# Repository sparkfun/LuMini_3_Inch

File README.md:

SparkFun LuMini 3 Inch Ring
========================================

[*LuMini LED Ring - 3 Inch (COM-14965)*](https://www.sparkfun.com/products/14965)

The LuMini rings are a great way to add high density light rings to your project. They use APA102 LEDs to provide bright colors and fast data rates.

Repository Contents
-------------------

* **/Firmware** - Example code 
* **/Hardware** - Eagle design files (.brd, .sch)

Documentation
--------------
* **[Installing an Arduino Library Guide](https://learn.sparkfun.com/tutorials/installing-an-arduino-library)** - Basic information on how to install an Arduino library.
* **[Library Repository](https://github.com/FastLED/FastLED)** - Arduino library for the APA102.
* **[Hookup Guide](https://learn.sparkfun.com/tutorials/lumini-ring-hookup-guide)** - Basic hookup guide for the LuMini Rings.

Product Versions
----------------
* [COM-14965](https://www.sparkfun.com/products/14965)- 3 Inch LED Ring

License Information
-------------------

This product is _**open source**_! 

Please review the LICENSE.md file for license information. 

If you have any questions or concerns on licensing, please contact techsupport@sparkfun.com.

Distributed as-is; no warranty is given.

- Your friends at SparkFun.

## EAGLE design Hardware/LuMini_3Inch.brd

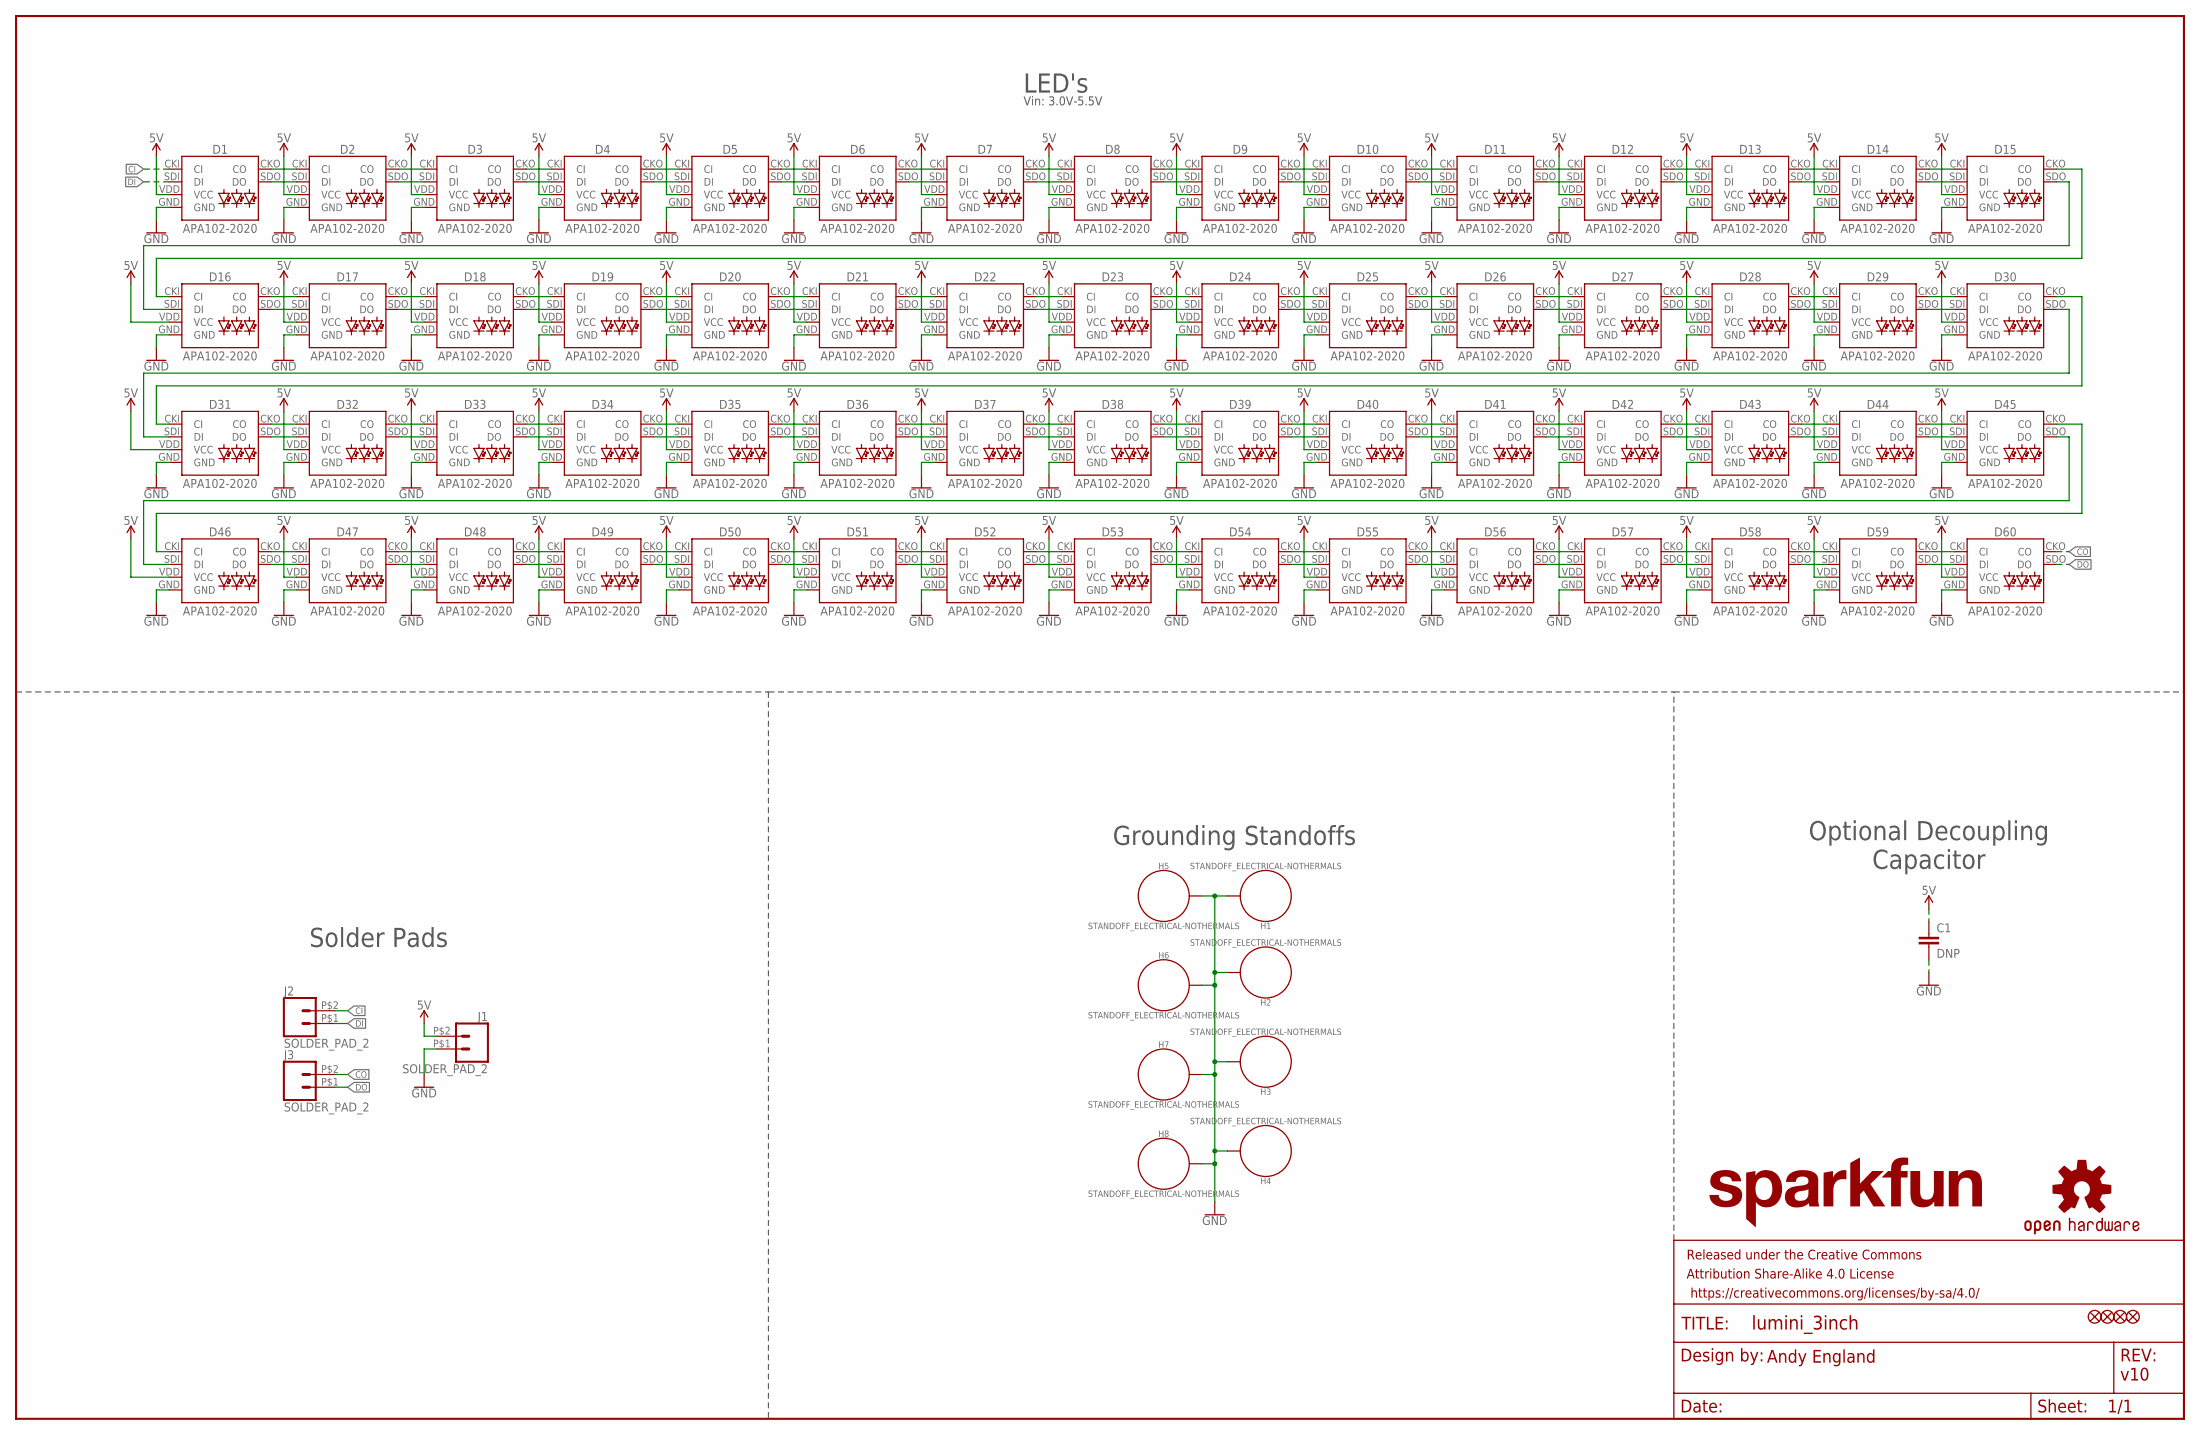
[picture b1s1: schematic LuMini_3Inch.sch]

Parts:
C1: DNP; 1206
D1, D2, D3, D4, D5, D6, D7, D8, D9, D10, D11, D12, D13, D14, D15, D16, D17, D18, D19, D20, D21, D22, D23, D24, D25, D26, D27, D28, D29, D30, D31, D32, D33, D34, D35, D36, D37, D38, D39, D40, D41, D42, D43, D44, D45, D46, D47, D48, D49, D50, D51, D52, D53, D54, D55, D56, D57, D58, D59, D60: APA102-2020
FD1, FD2, FD3, FD4: FIDUCIALUFIDUCIAL; FIDUCIAL-MICRO
FRAME1: FRAME-LEDGER; CREATIVE_COMMONS
H1, H2, H3, H4, H5, H6, H7, H8: STANDOFF_ELECTRICAL-NOTHERMALS; STANDOFF-ELECTRICAL-NOTHERMALS
J1, J2, J3: SOLDER_PAD_2
LOGO1: OSHW-LOGOS; OSHW-LOGO-S
LOGO2: SFE_LOGO_NAME.1_INCH; SFE_LOGO_NAME_.1

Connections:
5V: C1.1, D1.VDD (VCC), D2.VDD (VCC), D3.VDD (VCC), D4.VDD (VCC), D5.VDD (VCC), D6.VDD (VCC), D7.VDD (VCC), D8.VDD (VCC), D9.VDD (VCC), D10.VDD (VCC), D11.VDD (VCC), D12.VDD (VCC), D13.VDD (VCC), D14.VDD (VCC), D15.VDD (VCC), D16.VDD (VCC), D17.VDD (VCC), D18.VDD (VCC), D19.VDD (VCC), D20.VDD (VCC), D21.VDD (VCC), D22.VDD (VCC), D23.VDD (VCC), D24.VDD (VCC), D25.VDD (VCC), D26.VDD (VCC), D27.VDD (VCC), D28.VDD (VCC), D29.VDD (VCC), D30.VDD (VCC), D31.VDD (VCC), D32.VDD (VCC), D33.VDD (VCC), D34.VDD (VCC), D35.VDD (VCC), D36.VDD (VCC), D37.VDD (VCC), D38.VDD (VCC), D39.VDD (VCC), D40.VDD (VCC), D41.VDD (VCC), D42.VDD (VCC), D43.VDD (VCC), D44.VDD (VCC), D45.VDD (VCC), D46.VDD (VCC), D47.VDD (VCC), D48.VDD (VCC), D49.VDD (VCC), D50.VDD (VCC), D51.VDD (VCC), D52.VDD (VCC), D53.VDD (VCC), D54.VDD (VCC), D55.VDD (VCC), D56.VDD (VCC), D57.VDD (VCC), D58.VDD (VCC), D59.VDD (VCC), D60.VDD (VCC), J1.P$2 (2)
CI: D1.CKI (CI), J2.P$2 (2)
CO: D60.CKO (CO), J3.P$2 (2)
DI: D1.SDI (DI), J2.P$1 (1)
DO: D60.SDO (DO), J3.P$1 (1)
GND: C1.2, D1.GND, D2.GND, D3.GND, D4.GND, D5.GND, D6.GND, D7.GND, D8.GND, D9.GND, D10.GND, D11.GND, D12.GND, D13.GND, D14.GND, D15.GND, D16.GND, D17.GND, D18.GND, D19.GND, D20.GND, D21.GND, D22.GND, D23.GND, D24.GND, D25.GND, D26.GND, D27.GND, D28.GND, D29.GND, D30.GND, D31.GND, D32.GND, D33.GND, D34.GND, D35.GND, D36.GND, D37.GND, D38.GND, D39.GND, D40.GND, D41.GND, D42.GND, D43.GND, D44.GND, D45.GND, D46.GND, D47.GND, D48.GND, D49.GND, D50.GND, D51.GND, D52.GND, D53.GND, D54.GND, D55.GND, D56.GND, D57.GND, D58.GND, D59.GND, D60.GND, H1.P1, H2.P1, H3.P1, H4.P1, H5.P1, H6.P1, H7.P1, H8.P1, J1.P$1 (1)
unnamed: D4.CKO (CO), D5.CKI (CI)
unnamed: D1.CKO (CO), D2.CKI (CI)
unnamed: D1.SDO (DO), D2.SDI (DI)
unnamed: D2.CKO (CO), D3.CKI (CI)
unnamed: D2.SDO (DO), D3.SDI (DI)
unnamed: D3.CKO (CO), D4.CKI (CI)
unnamed: D3.SDO (DO), D4.SDI (DI)
unnamed: D4.SDO (DO), D5.SDI (DI)
unnamed: D5.CKO (CO), D6.CKI (CI)
unnamed: D5.SDO (DO), D6.SDI (DI)
unnamed: D6.CKO (CO), D7.CKI (CI)
unnamed: D6.SDO (DO), D7.SDI (DI)
unnamed: D7.CKO (CO), D8.CKI (CI)
unnamed: D7.SDO (DO), D8.SDI (DI)
unnamed: D16.SDO (DO), D17.SDI (DI)
unnamed: D20.SDO (DO), D21.SDI (DI)
unnamed: D9.CKO (CO), D10.CKI (CI)
unnamed: D9.SDO (DO), D10.SDI (DI)
unnamed: D10.CKO (CO), D11.CKI (CI)
unnamed: D10.SDO (DO), D11.SDI (DI)
unnamed: D11.CKO (CO), D12.CKI (CI)
unnamed: D11.SDO (DO), D12.SDI (DI)
unnamed: D12.CKO (CO), D13.CKI (CI)
unnamed: D12.SDO (DO), D13.SDI (DI)
unnamed: D13.CKO (CO), D14.CKI (CI)
unnamed: D13.SDO (DO), D14.SDI (DI)
unnamed: D14.CKO (CO), D15.CKI (CI)
unnamed: D14.SDO (DO), D15.SDI (DI)
unnamed: D45.CKO (CO), D46.CKI (CI)
unnamed: D30.CKO (CO), D31.CKI (CI)
unnamed: D8.CKO (CO), D9.CKI (CI)
unnamed: D8.SDO (DO), D9.SDI (DI)
unnamed: D17.CKO (CO), D18.CKI (CI)
unnamed: D17.SDO (DO), D18.SDI (DI)
unnamed: D18.CKO (CO), D19.CKI (CI)
unnamed: D18.SDO (DO), D19.SDI (DI)
unnamed: D19.CKO (CO), D20.CKI (CI)
unnamed: D19.SDO (DO), D20.SDI (DI)
unnamed: D30.SDO (DO), D31.SDI (DI)
unnamed: D15.CKO (CO), D16.CKI (CI)
unnamed: D16.CKO (CO), D17.CKI (CI)
unnamed: D21.CKO (CO), D22.CKI (CI)
unnamed: D21.SDO (DO), D22.SDI (DI)
unnamed: D22.CKO (CO), D23.CKI (CI)
unnamed: D22.SDO (DO), D23.SDI (DI)
unnamed: D23.CKO (CO), D24.CKI (CI)
unnamed: D23.SDO (DO), D24.SDI (DI)
unnamed: D24.CKO (CO), D25.CKI (CI)
unnamed: D24.SDO (DO), D25.SDI (DI)
unnamed: D25.CKO (CO), D26.CKI (CI)
unnamed: D25.SDO (DO), D26.SDI (DI)
unnamed: D26.CKO (CO), D27.CKI (CI)
unnamed: D26.SDO (DO), D27.SDI (DI)
unnamed: D27.CKO (CO), D28.CKI (CI)
unnamed: D27.SDO (DO), D28.SDI (DI)
unnamed: D29.CKO (CO), D30.CKI (CI)
unnamed: D29.SDO (DO), D30.SDI (DI)
unnamed: D15.SDO (DO), D16.SDI (DI)
unnamed: D45.SDO (DO), D46.SDI (DI)
unnamed: D31.CKO (CO), D32.CKI (CI)
unnamed: D31.SDO (DO), D32.SDI (DI)
unnamed: D32.CKO (CO), D33.CKI (CI)
unnamed: D32.SDO (DO), D33.SDI (DI)
unnamed: D33.CKO (CO), D34.CKI (CI)
unnamed: D33.SDO (DO), D34.SDI (DI)
unnamed: D34.CKO (CO), D35.CKI (CI)
unnamed: D34.SDO (DO), D35.SDI (DI)
unnamed: D35.CKO (CO), D36.CKI (CI)
unnamed: D35.SDO (DO), D36.SDI (DI)
unnamed: D37.CKO (CO), D38.CKI (CI)
unnamed: D37.SDO (DO), D38.SDI (DI)
unnamed: D38.SDO (DO), D39.SDI (DI)
unnamed: D39.CKO (CO), D40.CKI (CI)
unnamed: D39.SDO (DO), D40.SDI (DI)
unnamed: D38.CKO (CO), D39.CKI (CI)
unnamed: D28.CKO (CO), D29.CKI (CI)
unnamed: D28.SDO (DO), D29.SDI (DI)
unnamed: D36.SDO (DO), D37.SDI (DI)
unnamed: D36.CKO (CO), D37.CKI (CI)
unnamed: D40.CKO (CO), D41.CKI (CI)
unnamed: D40.SDO (DO), D41.SDI (DI)
unnamed: D41.CKO (CO), D42.CKI (CI)
unnamed: D41.SDO (DO), D42.SDI (DI)
unnamed: D42.CKO (CO), D43.CKI (CI)
unnamed: D42.SDO (DO), D43.SDI (DI)
unnamed: D43.CKO (CO), D44.CKI (CI)
unnamed: D43.SDO (DO), D44.SDI (DI)
unnamed: D44.CKO (CO), D45.CKI (CI)
unnamed: D44.SDO (DO), D45.SDI (DI)
unnamed: D46.CKO (CO), D47.CKI (CI)
unnamed: D46.SDO (DO), D47.SDI (DI)
unnamed: D47.CKO (CO), D48.CKI (CI)
unnamed: D47.SDO (DO), D48.SDI (DI)
unnamed: D49.CKO (CO), D50.CKI (CI)
unnamed: D49.SDO (DO), D50.SDI (DI)
unnamed: D50.CKO (CO), D51.CKI (CI)
unnamed: D50.SDO (DO), D51.SDI (DI)
unnamed: D51.CKO (CO), D52.CKI (CI)
unnamed: D51.SDO (DO), D52.SDI (DI)
unnamed: D52.CKO (CO), D53.CKI (CI)
unnamed: D52.SDO (DO), D53.SDI (DI)
unnamed: D53.CKO (CO), D54.CKI (CI)
unnamed: D53.SDO (DO), D54.SDI (DI)
unnamed: D54.CKO (CO), D55.CKI (CI)
unnamed: D54.SDO (DO), D55.SDI (DI)
unnamed: D55.CKO (CO), D56.CKI (CI)
unnamed: D55.SDO (DO), D56.SDI (DI)
unnamed: D57.CKO (CO), D58.CKI (CI)
unnamed: D57.SDO (DO), D58.SDI (DI)
unnamed: D58.SDO (DO), D59.SDI (DI)
unnamed: D59.CKO (CO), D60.CKI (CI)
unnamed: D59.SDO (DO), D60.SDI (DI)
unnamed: D58.CKO (CO), D59.CKI (CI)
unnamed: D48.CKO (CO), D49.CKI (CI)
unnamed: D48.SDO (DO), D49.SDI (DI)
unnamed: D56.SDO (DO), D57.SDI (DI)
unnamed: D56.CKO (CO), D57.CKI (CI)
unnamed: D20.CKO (CO), D21.CKI (CI)

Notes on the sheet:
LED's
Grounding Standoffs
Andy England
v10
Vin: 3.0V-5.5V
Optional Decoupling Capacitor
Solder Pads

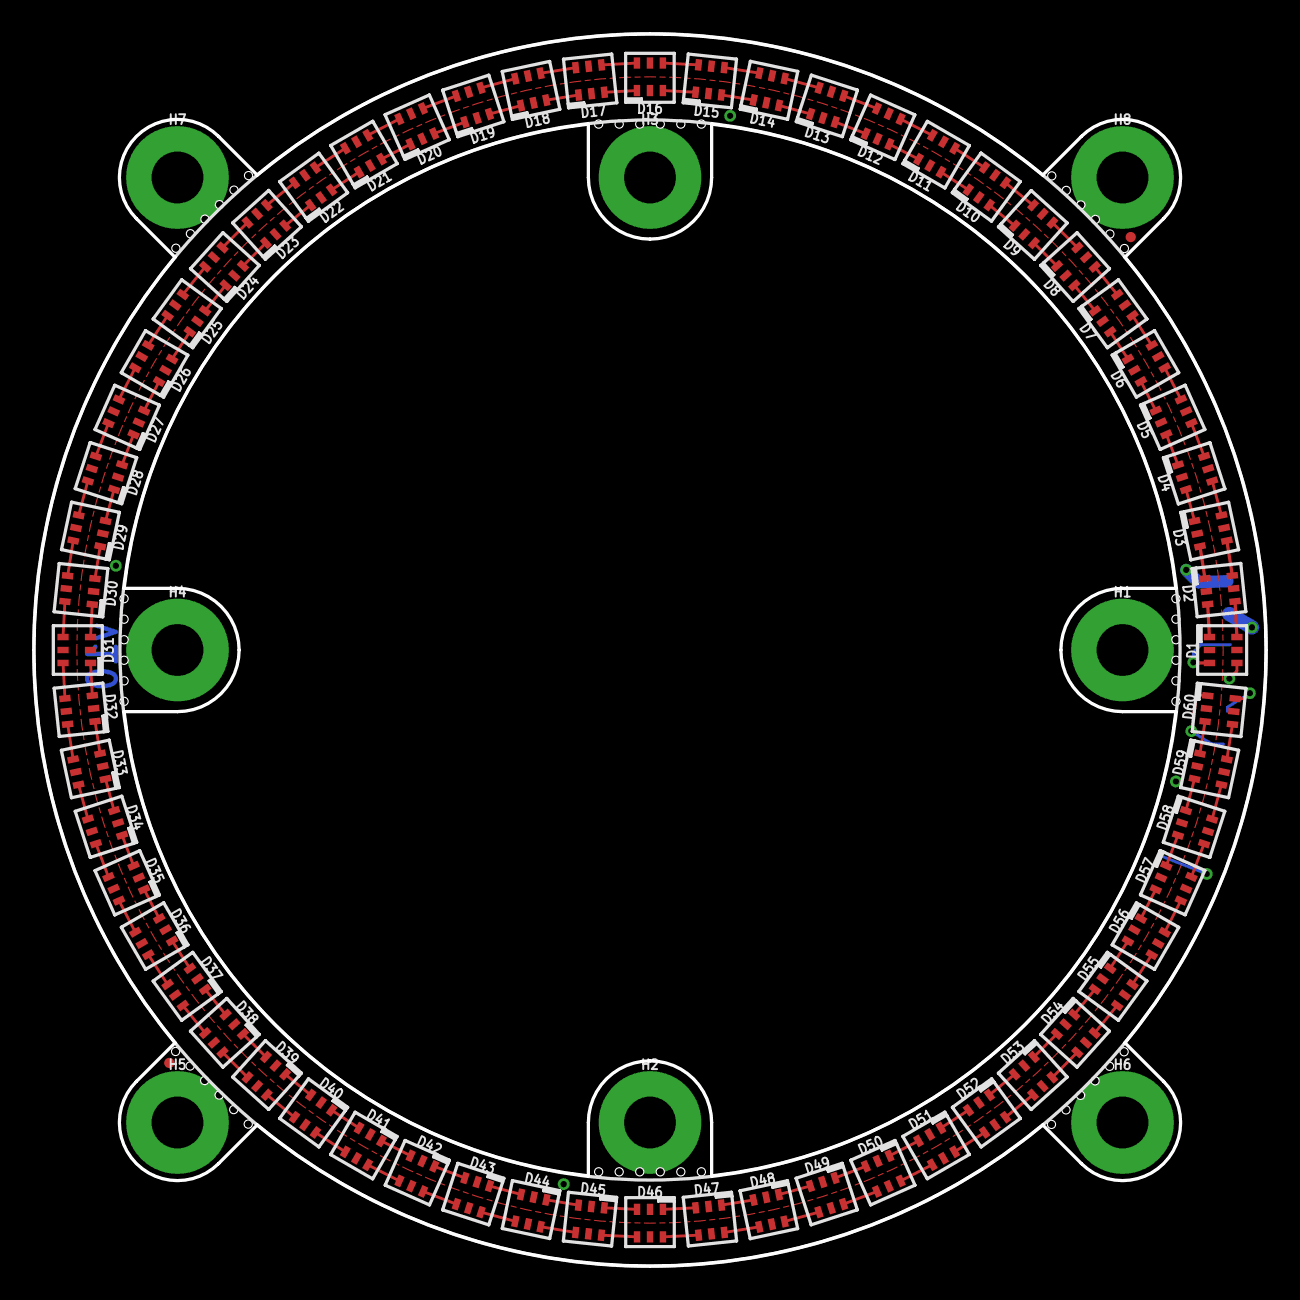
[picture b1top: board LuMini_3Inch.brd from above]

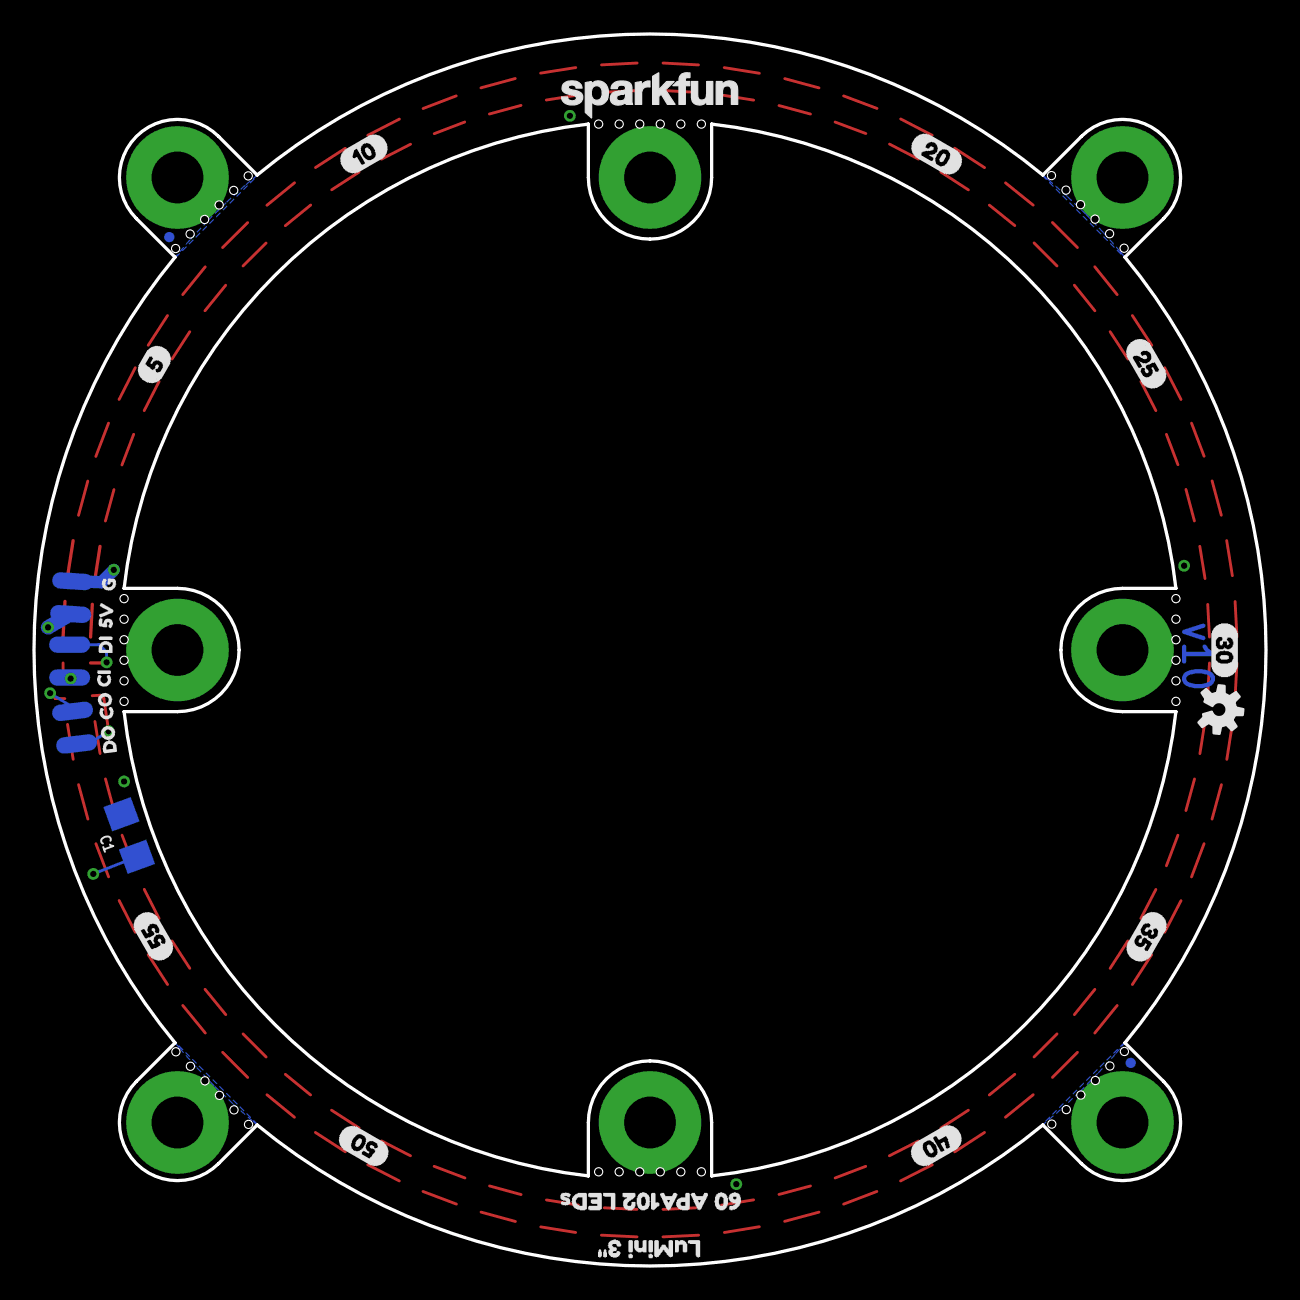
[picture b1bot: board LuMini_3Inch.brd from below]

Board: 2 copper layers, 76.2 x 76.2 mm, 97 parts (25 on the bottom side), 124 nets.

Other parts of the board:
U$1: LUMINI_3#2
U$2: 60_APA102_LEDS0
U$3: 54
U$4: 5V6
U$5: G4
U$6: 105
U$7: DO3
U$8: CO1
U$9: CI6
U$10: DI4
U$11: 207
U$12: 258
U$13: 309
U$14: 3510
U$15: 4011
U$16: 5013
U$17: 5514
U$18: ORDERING_INSTRUCTIONS

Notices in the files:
parts and their libraries:
SparkFun-LED: Licensing: Creative Commons ShareAlike 4.0 International - https://creativecommons.org/licenses/by-sa/4.0
SparkFun-Aesthetics: Released under the Creative Commons Attribution Share-Alike 4.0 License
SparkFun-Aesthetics: https://creativecommons.org/licenses/by-sa/4.0
